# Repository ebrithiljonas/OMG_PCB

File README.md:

# OMG PCB
# This Project is not up to date with the newest OpenMQTTGateway
All in One PCB for the [OpenMQTTGateway](https://github.com/1technophile/OpenMQTTGateway) Project

### Hardware
| Usage           | Hardware      |
|-----------------|---------------|
| Microcontroller | NodeMCU v1.0  |
| IR Receive      | TSOP21        |
| IR Send         | IR204A        |
| RF Receive      | SRX882        |
| RF Send         | STX882        |
| PIR             | SR505         |
| DHT             | DHT-11        |
| Bluetooth       | HM-10         |

Full BOM is [here](https://ebrithiljonas.github.io/OMG_PCB/ibom).
Attention! The ESP Board is the wrong type in the BOM, it's the NodeMCU v1.0, NOT the v0.9.
Download Gerber [here](https://ebrithiljonas.github.io/OMG_PCB/ibom).

### Configuration

The Pinout isn't exactly as the default from the OpenMQTTGateway
You need to change the pins like this:

```c++
// config_IR.h
#define IR_RECEIVER_PIN D4
#define IR_EMITTER_PIN D0

// config_RF.h
#define RF_RECEIVER_PIN D1
#define RF_EMITTER_PIN 3

// config_HCSR501.h
#define HCSR501_PIN D5

// config_DHT.h
#define DHT_SENSOR_TYPE DHT11 //uncomment for DHT11 Sensor
//#define DHT_SENSOR_TYPE DHT22 //uncomment for DHT22 Sensor (default for backwards compatibility)
#define DHT_RECEIVER_PIN D2

// config_BT.h
#define BT_RX D7
#define BT_TX D6
```

### Images

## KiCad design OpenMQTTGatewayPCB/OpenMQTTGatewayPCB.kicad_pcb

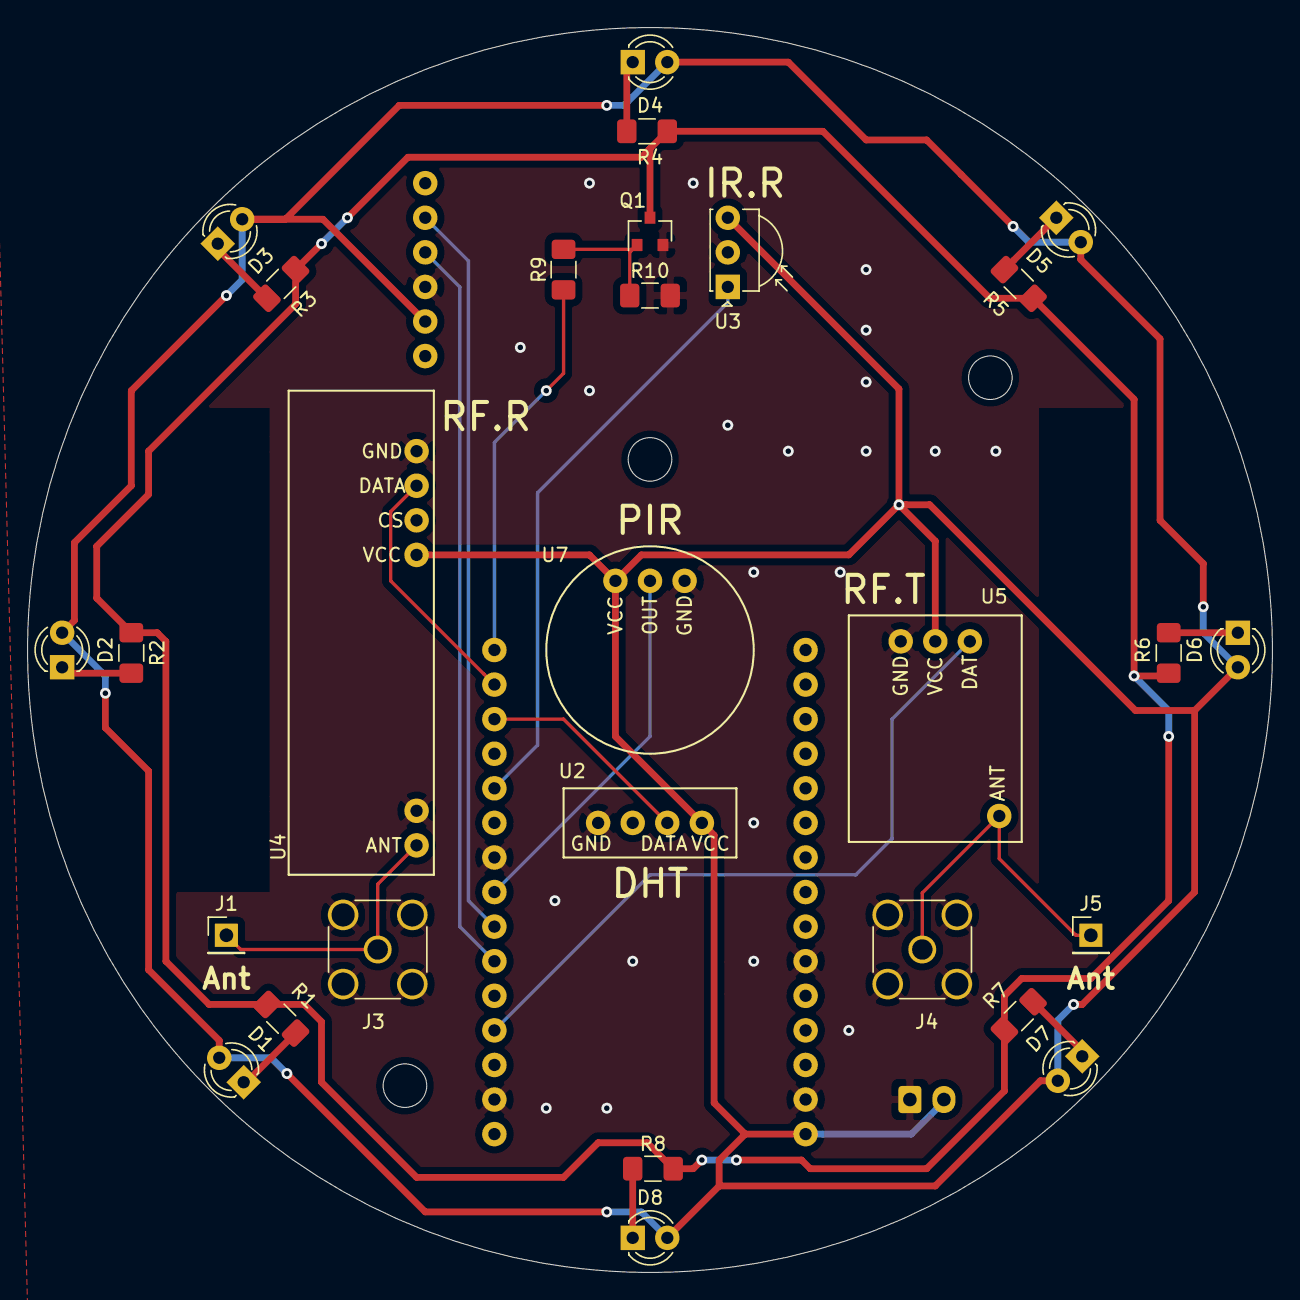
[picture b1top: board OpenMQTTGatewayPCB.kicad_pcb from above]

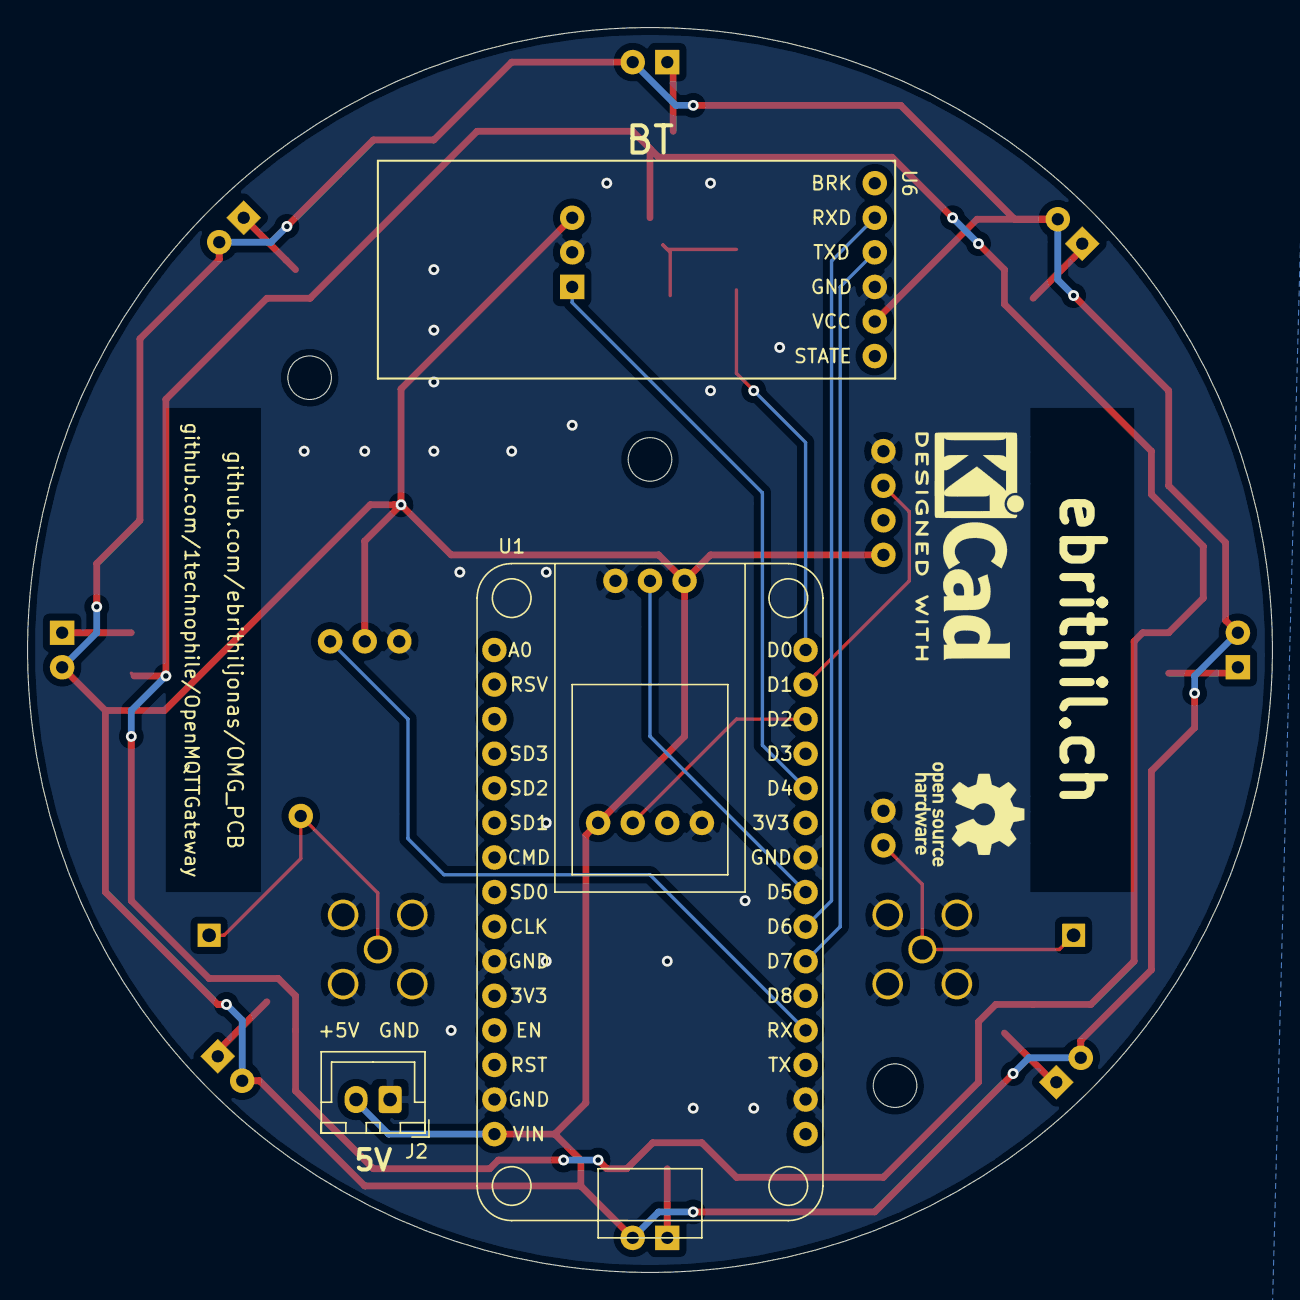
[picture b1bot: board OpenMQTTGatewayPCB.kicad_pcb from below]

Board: 2 copper layers, 91.4 x 91.4 mm, 31 parts (3 on the bottom side), 22 nets.

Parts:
D1, D2, D3, D4, D5, D6, D7, D8: IR204A; LED_D3.0mm_IRBlack
J1, J5: Antenna Con; PinHeader_1x01_P2.54mm_Vertical
J2: Conn_01x02_Male; JST_XH_B02B-XH-A_1x02_P2.50mm_Vertical
J3, J4: Conn_Coaxial; SMA_Amphenol_132291_Vertical
Q1: AO3402; SOT-23
R1, R2, R3, R4, R5, R6, R7, R8: 47R; R_1206_3216Metric_Pad1.42x1.75mm_HandSolder
R9, R10: 1K; R_1206_3216Metric_Pad1.42x1.75mm_HandSolder
U1: nodemcu_v0.9
U2: DHT11
U3: TSOP34S40F; Vishay_MOLD-3Pin
U4: SRX882
U5: STX882
U6: HM-10
U7: SR505

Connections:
+5V: D1.2, D2.2, D3.2, D4.2, D5.2, D6.2, D7.2, D8.2, J2.2, U1.15, U2.1, U3.3, U4.4, U5.2, U6.2, U7.3
D0: R9.1, U1.16
D1: U1.17, U4.2
D2: U1.18, U2.2
D4: U1.20, U3.1
D5: U1.23, U7.2
D6: U1.24, U6.5
D7: U1.25, U6.4
GND: J2.1, J3.2, J4.2, Q1.2, R10.2, U1.10, U1.14, U1.22, U1.29, U2.4, U3.2, U4.1, U5.3, U6.3, U7.1
unnamed: D1.1, R1.1
unnamed: D2.1, R2.1
unnamed: D3.1, R3.1
unnamed: D4.1, R4.1
unnamed: D5.1, R5.1
unnamed: D6.1, R6.1
unnamed: D7.1, R7.1
unnamed: D8.1, R8.1
unnamed: J1.1, J3.1, U4.5
unnamed: J4.1, J5.1, U5.4
unnamed: Q1.1, R9.2, R10.1
unnamed: Q1.3, R1.2, R2.2, R3.2, R4.2, R5.2, R6.2, R7.2, R8.2
RX: U1.27, U5.1

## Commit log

2019-07-31 Add Images of 3D PCB
2019-07-31 Add HTML BOM
2019-07-31 Added Silkscrean for Power input
2019-07-31 Generated Gerber Files
2019-08-15 Test Results Noted
2019-08-22 Fixed all known issues of rev1
2019-08-22 New Images
2019-09-18 Final touches for release
2019-09-24 Moved Gerber.zip to Documents folder
2019-09-24 Added link to OMG Project
2020-04-19 Added link to Project
2020-05-04 Fixed ESP board name
